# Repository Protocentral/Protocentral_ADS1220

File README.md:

# ProtoCentral ADS1220 24-bit ADC Breakout Board

If you don't already have one, you can buy the ProtoCentral ADS1220 24-bit ADC Breakout Board from: [ProtoCentral(Worldwide)](https://protocentral.com/product/ads1220-24-bit-4-channel-low-noise-adc-breakout-board/)

Why would you need a 24-bit ADC? When 16-bit is just not enough. If your design demands high precision analog measurements, this breakout board for the Texas Instruments [ADS1220](https://www.ti.com/product/ADS1220) 24-bit delta-sigma ADC can get the job done. The ADS1220 gets rid of almost all external components with an internal voltage reference and internal clock, and adds a built-in PGA, temperature sensor and two matched current sources for sensor excitation — making it one of the easiest to use 24-bit ADCs around.

This Arduino library provides a modern, fully-featured driver for the ADS1220.

## Features

* 24-bit, 4-channel (2 differential / 4 single-ended) delta-sigma ADC
* Programmable data rates: 20 SPS up to 2 kSPS (Turbo mode)
* Programmable gain amplifier (PGA): 1 V/V to 128 V/V
* Internal 2.048 V reference, internal oscillator, internal temperature sensor
* Two matched IDAC current sources (10 µA – 1.5 mA) for RTD/sensor excitation
* 50/60 Hz FIR notch filter and low-side power switch
* Low current (~250 µA) and low noise (90 nVRMS at 20 SPS)

### Library highlights

* Typed `enum` / `struct` configuration API (no more raw register magic numbers)
* Blocking and non-blocking (`...Async`) reads
* Automatic raw-counts → voltage conversion from the active reference and gain
* Internal temperature-sensor readout in °C
* Per-instance SPI bus selection and ESP32 custom-pin `begin(sck, miso, mosi)`

## Applications

* High-precision analog voltage measurement
* PT100 / PT1000 RTD temperature measurement
* Strain-gauge load cells and Wheatstone-bridge sensors
* High-precision chemical and industrial sensors

## Installation

Install **ProtoCentral ADS1220** from the Arduino Library Manager, or download this
repository as a ZIP and use *Sketch → Include Library → Add .ZIP Library...*.

## Wiring to your Arduino

| ADS1220 Pin | Function       | Arduino Uno | ESP32 (VSPI) |
|-------------|:--------------:|:-----------:|:------------:|
| DRDY        | Data Ready     | D2          | D2 / D4      |
| MISO        | SPI Data Out   | D12         | D19          |
| MOSI        | SPI Data In    | D11         | D23          |
| SCLK        | SPI Clock      | D13         | D18          |
| CS          | Chip Select    | D7          | D7 / D5      |
| DVDD        | Digital VDD    | +5V         | +3.3V        |
| DGND        | Digital Ground | GND         | GND          |
| AVDD        | Analog VDD     | +5V         | +3.3V        |
| AGND        | Analog Ground  | GND         | GND          |
| AIN0–AIN3   | Analog Inputs  | Signals     | Signals      |

## Quick start

```cpp
#include "Protocentral_ADS1220.h"

#define ADS1220_CS_PIN    7
#define ADS1220_DRDY_PIN  2

Protocentral_ADS1220 ads1220(ADS1220_CS_PIN, ADS1220_DRDY_PIN);

void setup() {
    Serial.begin(115200);
    if (!ads1220.begin()) {
        Serial.println("ADS1220 not detected!");
        while (1);
    }
    ads1220.setInputMux(ADS1220_MUX_AIN0_AIN1);   // differential AIN0 - AIN1
    ads1220.setGain(ADS1220_GAIN_1);
    ads1220.setDataRate(ADS1220_DR_330SPS);
    ads1220.setReference(ADS1220_REF_INTERNAL_2V048);
    ads1220.setConversionMode(false);             // single-shot
}

void loop() {
    float mv = ads1220.readVoltage() * 1000.0;
    Serial.println(mv, 4);
    delay(200);
}
```

## Examples

| # | Example | Showcases |
|---|---------|-----------|
| 01 | [Basic-SingleEnded-Read](examples/01-Basic-SingleEnded-Read) | Single-ended scan of AIN0–AIN3, voltage conversion |
| 02 | [Differential-Continuous-Stream](examples/02-Differential-Continuous-Stream) | Continuous mode, DRDY interrupt, async reads |
| 03 | [Internal-Temperature-Sensor](examples/03-Internal-Temperature-Sensor) | On-chip temperature sensor in °C/°F |
| 04 | [High-Resolution-PGA](examples/04-High-Resolution-PGA) | PGA gain sweep 1×→128×, microvolt resolution |
| 05 | [RTD-PT100-3Wire](examples/05-RTD-PT100-3Wire) | 3-wire PT100 with dual IDAC sources, ratiometric reference |
| 06 | [Loadcell-Wheatstone-Bridge](examples/06-Loadcell-Wheatstone-Bridge) | Ratiometric bridge/load-cell sensing with tare |
| 07 | [Register-Dump-Diagnostics](examples/07-Register-Dump-Diagnostics) | `ADS1220_Config`, register dump, diagnostic MUX |
| 08 | [ESP32-MultiSPI](examples/08-ESP32-MultiSPI) | Custom SPI bus and ESP32 `begin(sck, miso, mosi)` |

To compile all examples locally with `arduino-cli`:

```bash
cd examples
./compile_examples.sh                 # defaults to arduino:avr:uno
./compile_examples.sh esp32:esp32:esp32
```

## API overview

```cpp
// Construction
Protocentral_ADS1220 ads1220();                          // default pins (CS 7, DRDY 2)
Protocentral_ADS1220 ads1220(csPin, drdyPin);
Protocentral_ADS1220 ads1220(csPin, drdyPin, &SPI1);     // custom SPI bus

// Initialisation
bool begin(bool startSPI = true);
bool begin(const ADS1220_Config& config, bool startSPI = true);
bool begin(uint8_t sck, uint8_t miso, uint8_t mosi);     // ESP32

// Configuration
setDataRate, setOperatingMode, setGain, enablePGA, setInputMux,
setReference, setReferenceVoltage, setFIRFilter, setConversionMode,
enableTemperatureSensor, enableBurnoutSources,
setIDACCurrent, setIDAC1Route, setIDAC2Route,
enableLowSideSwitch, setDRDYOnDOUT

// Acquisition
startConversion, stopConversion, isDataReady,
readRaw, readVoltage, readRawAsync, readVoltageAsync,
readSingleEnded, readTemperature

// Utility
reset, testConnection, writeRegister, readRegister,
getConfigRegisters, printRegisters,
countsToVoltage, voltageToCounts, getLibraryVersion
```

## Migrating from v1.x

Version 2.0.0 is a clean rewrite with a new API; sketches written for v1.x will
not compile unchanged. The mapping is direct:

| v1.x | v2.0.0 |
|------|--------|
| `pc_ads1220.begin(cs, drdy)` | `ads1220.begin()` (pins go to the constructor) |
| `set_data_rate(DR_330SPS)` | `setDataRate(ADS1220_DR_330SPS)` |
| `set_pga_gain(PGA_GAIN_1)` | `setGain(ADS1220_GAIN_1)` |
| `select_mux_channels(MUX_AIN0_AIN1)` | `setInputMux(ADS1220_MUX_AIN0_AIN1)` |
| `set_conv_mode_continuous()` | `setConversionMode(true)` |
| `Read_SingleShot_SingleEnded_WaitForData(MUX_SE_CH0)` | `readSingleEnded(0)` |
| `Read_Data_Samples()` / `Read_WaitForData()` | `readRaw()` / `readVoltage()` |
| `internal_reference()` | `setReference(ADS1220_REF_INTERNAL_2V048)` |

License Information
===================

This product is open source! Both, our hardware and software are open source and licensed under the following licenses:

Hardware
---------

**All hardware is released under the [CERN-OHL-P v2](https://ohwr.org/cern_ohl_p_v2.txt)** license.

Copyright CERN 2020.

This source describes Open Hardware and is licensed under the CERN-OHL-P v2.

You may redistribute and modify this documentation and make products
using it under the terms of the CERN-OHL-P v2 (https:/cern.ch/cern-ohl).
This documentation is distributed WITHOUT ANY EXPRESS OR IMPLIED
WARRANTY, INCLUDING OF MERCHANTABILITY, SATISFACTORY QUALITY
AND FITNESS FOR A PARTICULAR PURPOSE. Please see the CERN-OHL-P v2
for applicable conditions

Software
--------

**All software is released under the MIT License(http://opensource.org/licenses/MIT).**

THE SOFTWARE IS PROVIDED "AS IS", WITHOUT WARRANTY OF ANY KIND, EXPRESS OR IMPLIED, INCLUDING BUT NOT LIMITED TO THE WARRANTIES OF MERCHANTABILITY, FITNESS FOR A PARTICULAR PURPOSE AND NONINFRINGEMENT. IN NO EVENT SHALL THE AUTHORS OR COPYRIGHT HOLDERS BE LIABLE FOR ANY CLAIM, DAMAGES OR OTHER LIABILITY, WHETHER IN AN ACTION OF CONTRACT, TORT OR OTHERWISE, ARISING FROM, OUT OF OR IN CONNECTION WITH THE SOFTWARE OR THE USE OR OTHER DEALINGS IN THE SOFTWARE.

Documentation
-------------
**All documentation is released under [Creative Commons Share-alike 4.0 International](http://creativecommons.org/licenses/by-sa/4.0/).**

You are free to:

* Share — copy and redistribute the material in any medium or format
* Adapt — remix, transform, and build upon the material for any purpose, even commercially.
The licensor cannot revoke these freedoms as long as you follow the license terms.

Under the following terms:

* Attribution — You must give appropriate credit, provide a link to the license, and indicate if changes were made. You may do so in any reasonable manner, but not in any way that suggests the licensor endorses you or your use.
* ShareAlike — If you remix, transform, or build upon the material, you must distribute your contributions under the same license as the original.

Please check [*LICENSE.md*](LICENSE.md) for detailed license descriptions.

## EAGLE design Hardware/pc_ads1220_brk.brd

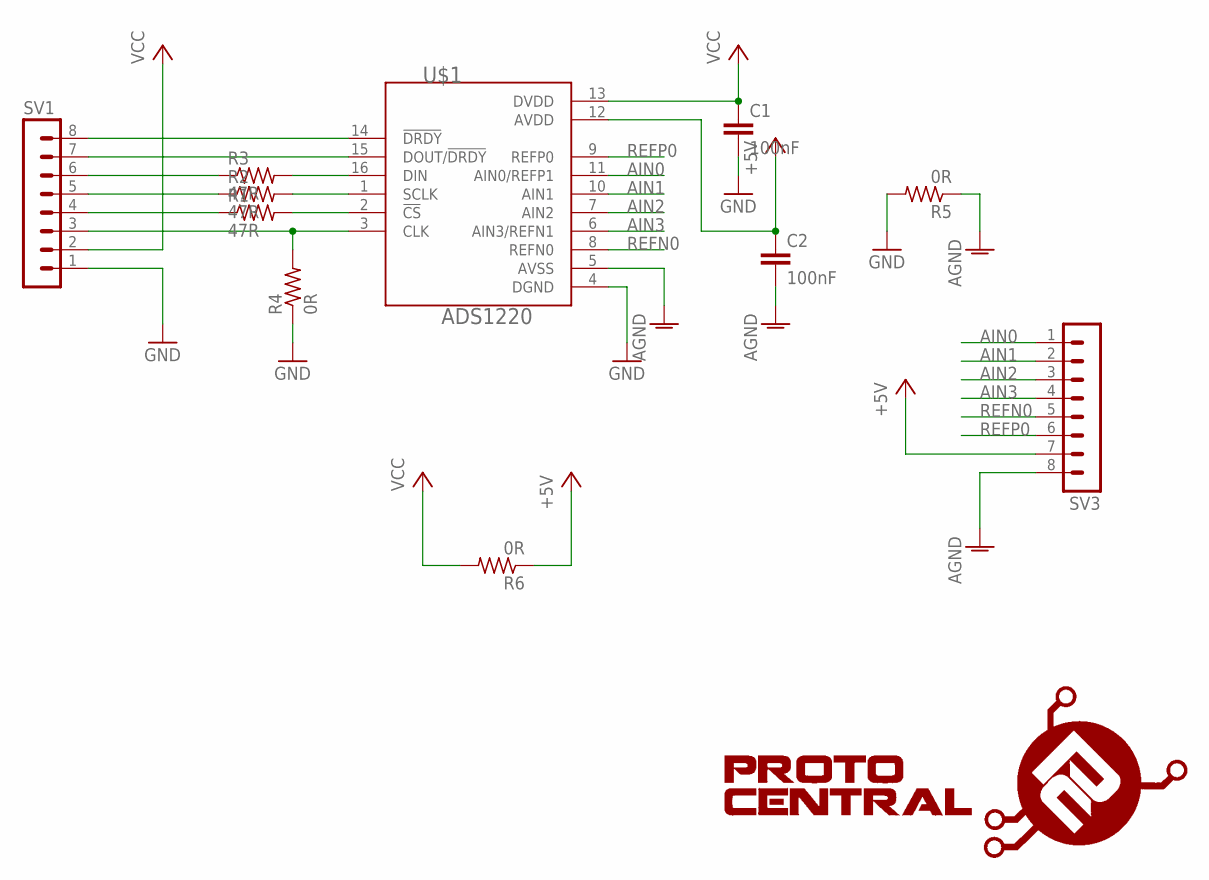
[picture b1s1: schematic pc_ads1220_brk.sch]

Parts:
C1, C2: 100nF; C0805
R1, R2, R3: 47R; R0805
R4, R5, R6: 0R; R0805
SV1, SV3: MA08-1
U$1: ADS1220; TSSOP-16
U$3: PROTY_LOGO_WITH_TEXT; PROTY_WITH_TEXT

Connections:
+5V: C2.1, R6.1, SV3.7, U$1.12 (AVDD)
AGND: C2.2, R5.1, SV3.8, U$1.5 (AVSS)
AIN0: SV3.1, U$1.11 (AIN0/REFP1)
AIN1: SV3.2, U$1.10 (AIN1)
AIN2: SV3.3, U$1.7 (AIN2)
AIN3: SV3.4, U$1.6 (AIN3/REFN1)
GND: C1.2, R4.1, R5.2, SV1.1, U$1.4 (DGND)
unnamed: R3.1, SV1.6
unnamed: R2.1, SV1.5
unnamed: R3.2, U$1.16 (DIN)
unnamed: R2.2, U$1.1 (SCLK)
unnamed: R1.2, U$1.2 (!CS)
unnamed: R1.1, SV1.4
unnamed: R4.2, SV1.3, U$1.3 (CLK)
unnamed: SV1.7, U$1.15 (DOUT/!DRDY)
unnamed: SV1.8, U$1.14 (!DRDY)
REFN0: SV3.5, U$1.8 (REFN0)
REFP0: SV3.6, U$1.9 (REFP0)
VCC: C1.1, R6.2, SV1.2, U$1.13 (DVDD)

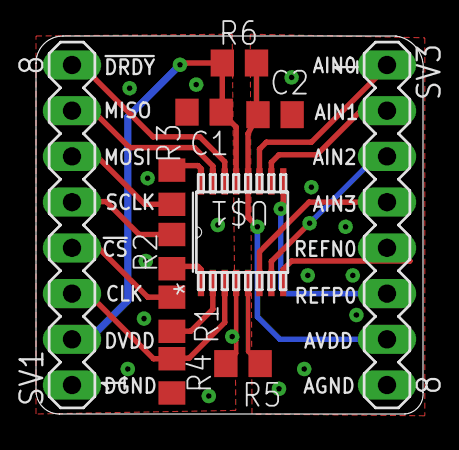
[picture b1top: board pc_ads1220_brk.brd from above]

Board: 4 copper layers, 21.5 x 21.0 mm, 12 parts (1 on the bottom side), 19 nets.

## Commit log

2014-08-11 :circus_tent: Added .gitattributes & .gitignore files
2014-08-11 Protocentral_ADS1220
    Breakout board for ads1220.
2015-10-28 Arduino Source file and Example Sketch
2015-10-28 Schematic and Design File
2015-10-28 Datasheet
2016-11-18 Updated license information
2018-04-19 Added images, edited README, added library properties
2018-04-19 Corrected mistakes in README
2018-04-19 Fix example folder
2018-04-19 Added header information
2018-06-17 Removed junk
2018-06-17 Encapsulated Read and Wait for data
2018-06-17 Cleaned up again, tested with Sensything
2018-06-17 Added new example - Sequential Read
2018-06-18 Added new example Read Sequential
2018-06-18 Updated read-sequential example
2018-06-18 Removed sensything tag
2018-06-19 Fixed issue with chip getting stuck
2018-06-19 Bump version number
2018-10-08 * Remove long delays. * Refactor repeated code. * Add functions to change the voltage reference. * Fix WaitForData * Remove Serial.print from begin()
2018-10-08 Add timeout to the WaitForData function.
2018-10-08 Fix a typo
2018-10-08 Add an include guard.
2018-10-08 Fix some warnings.
2018-10-08 Fix a bug in the reference selection code
2018-10-09 Use SPI transactions
2021-01-05 added interrupt based read
2021-02-13 Update Protocentral_ADS1220.cpp
    Added functions to control registers 0 -3 configuration following datasheet, including switching on/off internal Temp-sensor & operation mode etc.
2021-02-13 Update Protocentral_ADS1220.h
    Added functions to control registers 0 -3 configuration following datasheet, including switching on/off internal Temp-sensor & operation mode etc.
2021-02-13 Update Example2-ADS1220-Stream.ino
    Example for read out internal Temp added
2021-03-26 Update License Mark
2021-03-27 Update license info
2022-11-18 Adding CI build action
2022-11-18 Adding CI compile badge to README
2022-11-25 Fix merge conflicts
2022-11-25 Fixed example sketches
2022-11-25 Bump version
2023-09-16 Add C++ implementation for Raspberry Pi
2026-06-12 Rewrite ADS1220 library to v2.0.0 with modern enum/struct API
    - New typed enum/struct configuration API with Doxygen docs (clean break from v1.x)
    - Blocking and non-blocking (async) reads, auto voltage conversion
    - Per-instance SPI bus selection and ESP32 custom-pin begin()
    - Internal temperature sensor, dual IDAC, FIR filter, low-side switch support
    - Expand examples 2 -> 8 (single-ended, differential stream, temperature,
    PGA sweep, 3-wire PT100 RTD, Wheatstone bridge, diagnostics, ESP32 multi-SPI)
2026-06-13 Finalise plan

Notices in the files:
README.md:
CC-BY-SA-4.0
